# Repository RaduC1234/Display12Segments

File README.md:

# Display12Segments

Created in 2021. Uploaded here for arhive purposes.

The project includes an embedded device that i developed in 2021. Hardware created in Autodesk Eagle and software in MPLAB IDE and Visual Studio Code.

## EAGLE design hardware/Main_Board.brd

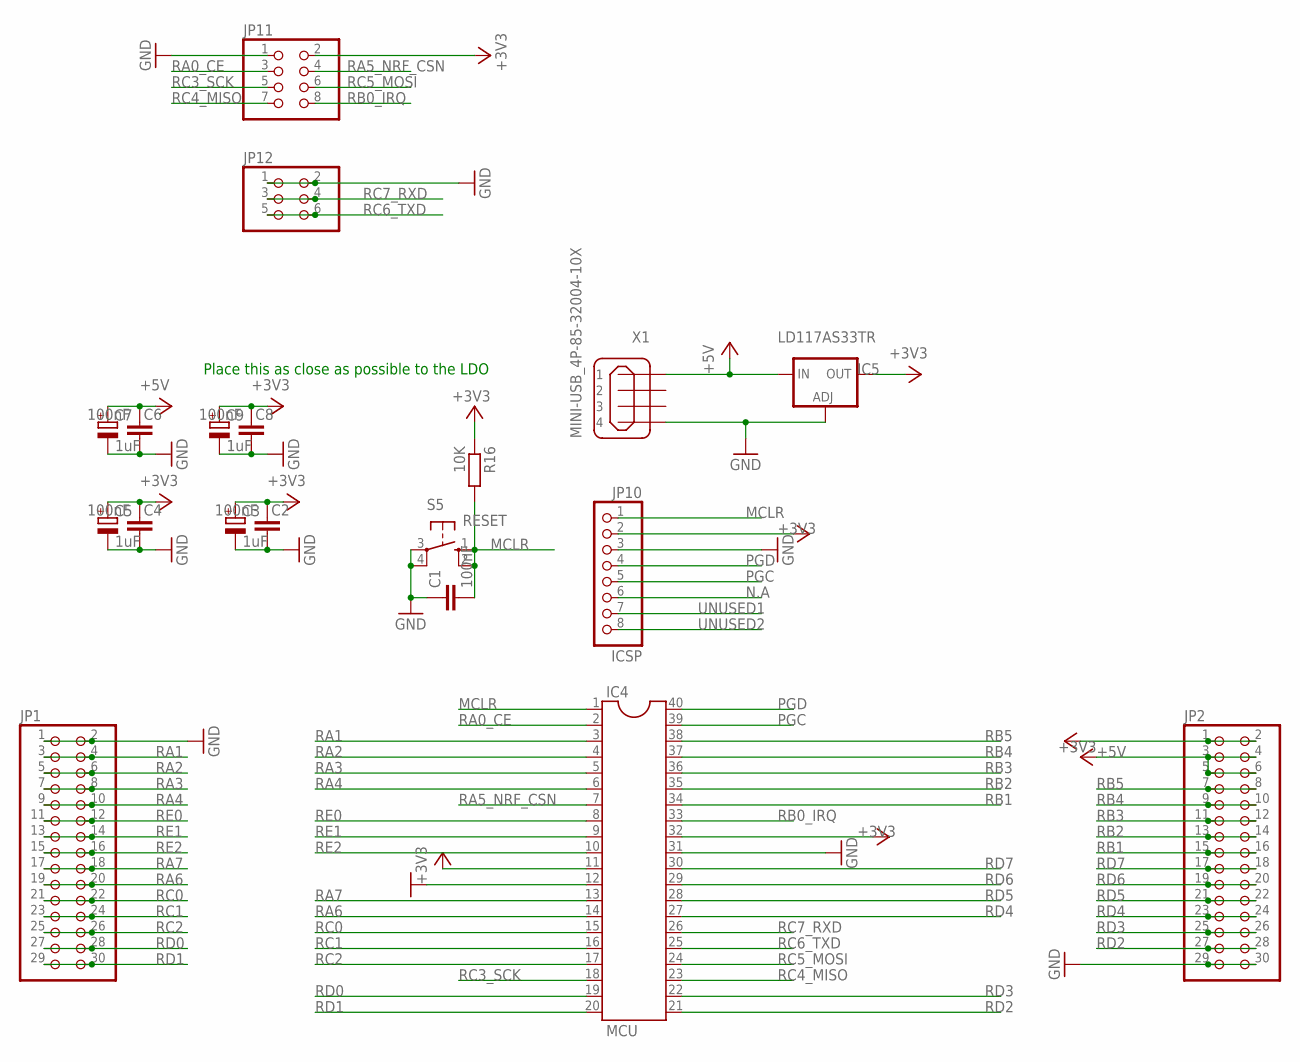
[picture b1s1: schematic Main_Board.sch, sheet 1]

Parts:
C1, C2, C4, C6, C8: 100nF; C025-025X050
C3, C5, C7, C9: 1uF; E1,8-4
IC4: MCU; DIL40
IC5: LD117AS33TR; SOT223
JP1, JP2: PINHD-2X15; 2X15
JP10: ICSP; 1X08
JP11: PINHD-2X4; 2X04
JP12: PINHD-2X3; 2X03
R16: 10K; 0207/10
S5: RESET; B3F-10XX
X1: MINI-USB_4P-85-32004-10X; 85-32004-10X

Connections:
+3V3: C2.2, C3.+, C4.2, C5.+, C8.2, C9.+, IC4.11, IC4.32, IC5.4 (OUT), JP2.1, JP2.2, JP10.2, JP11.2, R16.1; also elsewhere on the board
+5V: C6.2, C7.+, IC5.3 (IN), JP2.3, JP2.4, JP2.5, JP2.6, X1.1; also elsewhere on the board
GND: C1.1, C2.1, C3.-, C4.1, C5.-, C6.1, C7.-, C8.1, C9.-, IC4.12, IC4.31, IC5.1 (ADJ), JP1.1, JP1.2, JP2.29, JP2.30, JP10.3, JP11.1, JP12.1, JP12.2, S5.3, S5.4 (P1), X1.4; also elsewhere on the board
MCLR: C1.2, IC4.1, JP10.1, R16.2, S5.1 (S), S5.2 (S1)
N.A: JP10.6
PGC: IC4.39, JP10.5
PGD: IC4.40, JP10.4
RA0_CE: IC4.2, JP11.3
RA1: IC4.3, JP1.3, JP1.4
RA2: IC4.4, JP1.5, JP1.6
RA3: IC4.5, JP1.7, JP1.8
RA4: IC4.6, JP1.9, JP1.10
RA5_NRF_CSN: IC4.7, JP11.4
RA6: IC4.14, JP1.19, JP1.20
RA7: IC4.13, JP1.17, JP1.18
RB0_IRQ: IC4.33, JP11.8
RB1: IC4.34, JP2.15, JP2.16
RB2: IC4.35, JP2.13, JP2.14
RB3: IC4.36, JP2.11, JP2.12
RB4: IC4.37, JP2.9, JP2.10
RB5: IC4.38, JP2.7, JP2.8
RC0: IC4.15, JP1.21, JP1.22
RC1: IC4.16, JP1.23, JP1.24
RC2: IC4.17, JP1.25, JP1.26
RC3_SCK: IC4.18, JP11.5
RC4_MISO: IC4.23, JP11.7
RC5_MOSI: IC4.24, JP11.6
RC6_TXD: IC4.25, JP12.5, JP12.6
RC7_RXD: IC4.26, JP12.3, JP12.4
RD0: IC4.19, JP1.27, JP1.28
RD1: IC4.20, JP1.29, JP1.30
RD2: IC4.21, JP2.27, JP2.28
RD3: IC4.22, JP2.25, JP2.26
RD4: IC4.27, JP2.23, JP2.24
RD5: IC4.28, JP2.21, JP2.22
RD6: IC4.29, JP2.19, JP2.20
RD7: IC4.30, JP2.17, JP2.18
RE0: IC4.8, JP1.11, JP1.12
RE1: IC4.9, JP1.13, JP1.14
RE2: IC4.10, JP1.15, JP1.16
UNUSED1: JP10.7
UNUSED2: JP10.8

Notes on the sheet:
Place this as close as possible to the LDO

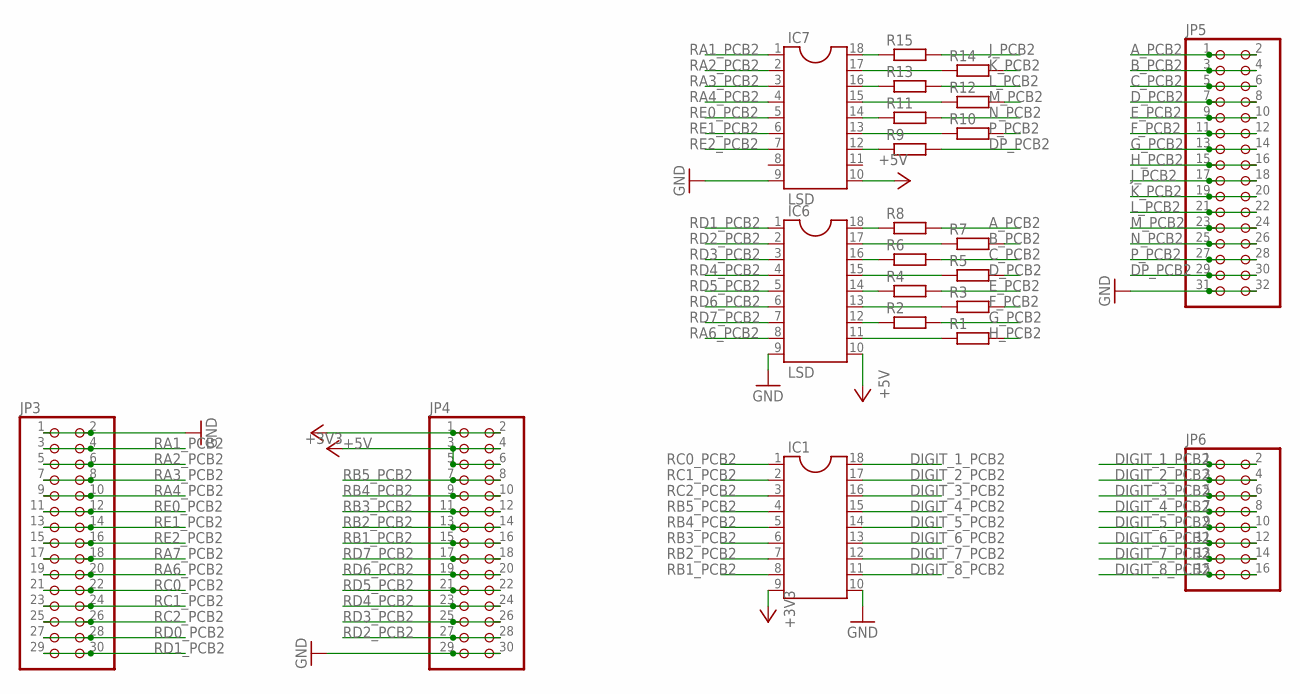
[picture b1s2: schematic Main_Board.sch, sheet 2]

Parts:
IC1: DIL18
IC6, IC7: LSD; DIL18
JP3, JP4: PINHD-2X15; 2X15
JP5: PINHD-2X16; 2X16
JP6: PINHD-2X8; 2X08
R1, R2, R3, R4, R5, R6, R7, R8, R9, R10, R11, R12, R13, R14, R15: R-EU_R0805; R0805

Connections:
+3V3: IC1.9, JP4.1, JP4.2; also elsewhere on the board
+5V: IC6.10, IC7.10, JP4.3, JP4.4, JP4.5, JP4.6; also elsewhere on the board
A_PCB2: JP5.1, JP5.2, R8.2
B_PCB2: JP5.3, JP5.4, R7.2
C_PCB2: JP5.5, JP5.6, R6.2
DIGIT_1_PCB2: IC1.18, JP6.1, JP6.2
DIGIT_2_PCB2: IC1.17, JP6.3, JP6.4
DIGIT_3_PCB2: IC1.16, JP6.5, JP6.6
DIGIT_4_PCB2: IC1.15, JP6.7, JP6.8
DIGIT_5_PCB2: IC1.14, JP6.9, JP6.10
DIGIT_6_PCB2: IC1.13, JP6.11, JP6.12
DIGIT_7_PCB2: IC1.12, JP6.13, JP6.14
DIGIT_8_PCB2: IC1.11, JP6.15, JP6.16
DP_PCB2: JP5.29, JP5.30, R9.2
D_PCB2: JP5.7, JP5.8, R5.2
E_PCB2: JP5.9, JP5.10, R4.2
F_PCB2: JP5.11, JP5.12, R3.2
GND: IC1.10, IC6.9, IC7.9, JP3.1, JP3.2, JP4.29, JP4.30, JP5.31, JP5.32; also elsewhere on the board
G_PCB2: JP5.13, JP5.14, R2.2
H_PCB2: JP5.15, JP5.16, R1.2
J_PCB2: JP5.17, JP5.18, R15.2
K_PCB2: JP5.19, JP5.20, R14.2
L_PCB2: JP5.21, JP5.22, R13.2
M_PCB2: JP5.23, JP5.24, R12.2
unnamed: IC6.18, R8.1
unnamed: IC6.17, R7.1
unnamed: IC6.16, R6.1
unnamed: IC6.15, R5.1
unnamed: IC6.14, R4.1
unnamed: IC6.13, R3.1
unnamed: IC6.12, R2.1
unnamed: IC6.11, R1.1
unnamed: IC7.18, R15.1
unnamed: IC7.17, R14.1
unnamed: IC7.16, R13.1
unnamed: IC7.15, R12.1
unnamed: IC7.14, R11.1
unnamed: IC7.13, R10.1
unnamed: IC7.12, R9.1
N_PCB2: JP5.25, JP5.26, R11.2
P_PCB2: JP5.27, JP5.28, R10.2
RA1_PCB2: IC7.1, JP3.3, JP3.4
RA2_PCB2: IC7.2, JP3.5, JP3.6
RA3_PCB2: IC7.3, JP3.7, JP3.8
RA4_PCB2: IC7.4, JP3.9, JP3.10
RA6_PCB2: IC6.8, JP3.19, JP3.20
RA7_PCB2: JP3.17, JP3.18
RB1_PCB2: IC1.8, JP4.15, JP4.16
RB2_PCB2: IC1.7, JP4.13, JP4.14
RB3_PCB2: IC1.6, JP4.11, JP4.12
RB4_PCB2: IC1.5, JP4.9, JP4.10
RB5_PCB2: IC1.4, JP4.7, JP4.8
RC0_PCB2: IC1.1, JP3.21, JP3.22
RC1_PCB2: IC1.2, JP3.23, JP3.24
RC2_PCB2: IC1.3, JP3.25, JP3.26
RD0_PCB2: JP3.27, JP3.28
RD1_PCB2: IC6.1, JP3.29, JP3.30
RD2_PCB2: IC6.2, JP4.27, JP4.28
RD3_PCB2: IC6.3, JP4.25, JP4.26
RD4_PCB2: IC6.4, JP4.23, JP4.24
RD5_PCB2: IC6.5, JP4.21, JP4.22
RD6_PCB2: IC6.6, JP4.19, JP4.20
RD7_PCB2: IC6.7, JP4.17, JP4.18
RE0_PCB2: IC7.5, JP3.11, JP3.12
RE1_PCB2: IC7.6, JP3.13, JP3.14
RE2_PCB2: IC7.7, JP3.15, JP3.16

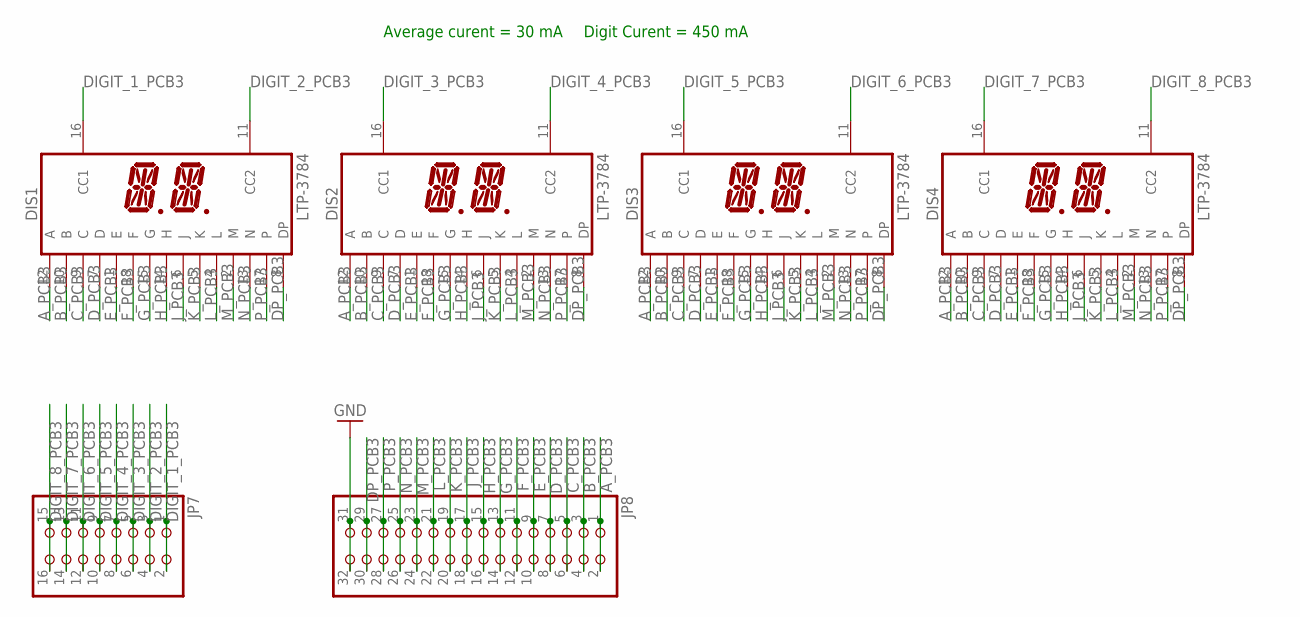
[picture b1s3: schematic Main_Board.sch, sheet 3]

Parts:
DIS1, DIS2, DIS3, DIS4: LTP-3784
JP7: PINHD-2X8; 2X08
JP8: PINHD-2X16; 2X16

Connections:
A_PCB3: DIS1.12 (A), DIS2.12 (A), DIS3.12 (A), DIS4.12 (A), JP8.1, JP8.2
B_PCB3: DIS1.10 (B), DIS2.10 (B), DIS3.10 (B), DIS4.10 (B), JP8.3, JP8.4
C_PCB3: DIS1.9 (C), DIS2.9 (C), DIS3.9 (C), DIS4.9 (C), JP8.5, JP8.6
DIGIT_1_PCB3: DIS1.16 (CC1), JP7.1, JP7.2
DIGIT_2_PCB3: DIS1.11 (CC2), JP7.3, JP7.4
DIGIT_3_PCB3: DIS2.16 (CC1), JP7.5, JP7.6
DIGIT_4_PCB3: DIS2.11 (CC2), JP7.7, JP7.8
DIGIT_5_PCB3: DIS3.16 (CC1), JP7.9, JP7.10
DIGIT_6_PCB3: DIS3.11 (CC2), JP7.11, JP7.12
DIGIT_7_PCB3: DIS4.16 (CC1), JP7.13, JP7.14
DIGIT_8_PCB3: DIS4.11 (CC2), JP7.15, JP7.16
DP_PCB3: DIS1.8 (DP), DIS2.8 (DP), DIS3.8 (DP), DIS4.8 (DP), JP8.29, JP8.30
D_PCB3: DIS1.7 (D), DIS2.7 (D), DIS3.7 (D), DIS4.7 (D), JP8.7, JP8.8
E_PCB3: DIS1.1 (E), DIS2.1 (E), DIS3.1 (E), DIS4.1 (E), JP8.9, JP8.10
F_PCB3: DIS1.18 (F), DIS2.18 (F), DIS3.18 (F), DIS4.18 (F), JP8.11, JP8.12
GND: JP8.31, JP8.32; also elsewhere on the board
G_PCB3: DIS1.15 (G), DIS2.15 (G), DIS3.15 (G), DIS4.15 (G), JP8.13, JP8.14
H_PCB3: DIS1.14 (H), DIS2.14 (H), DIS3.14 (H), DIS4.14 (H), JP8.15, JP8.16
J_PCB3: DIS1.6 (J), DIS2.6 (J), DIS3.6 (J), DIS4.6 (J), JP8.17, JP8.18
K_PCB3: DIS1.5 (K), DIS2.5 (K), DIS3.5 (K), DIS4.5 (K), JP8.19, JP8.20
L_PCB3: DIS1.4 (L), DIS2.4 (L), DIS3.4 (L), DIS4.4 (L), JP8.21, JP8.22
M_PCB3: DIS1.2 (M), DIS2.2 (M), DIS3.2 (M), DIS4.2 (M), JP8.23, JP8.24
N_PCB3: DIS1.13 (N), DIS2.13 (N), DIS3.13 (N), DIS4.13 (N), JP8.25, JP8.26
P_PCB3: DIS1.17, DIS2.17, DIS3.17, DIS4.17, JP8.27, JP8.28

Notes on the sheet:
Average curent = 30 mA
Digit Curent = 450 mA

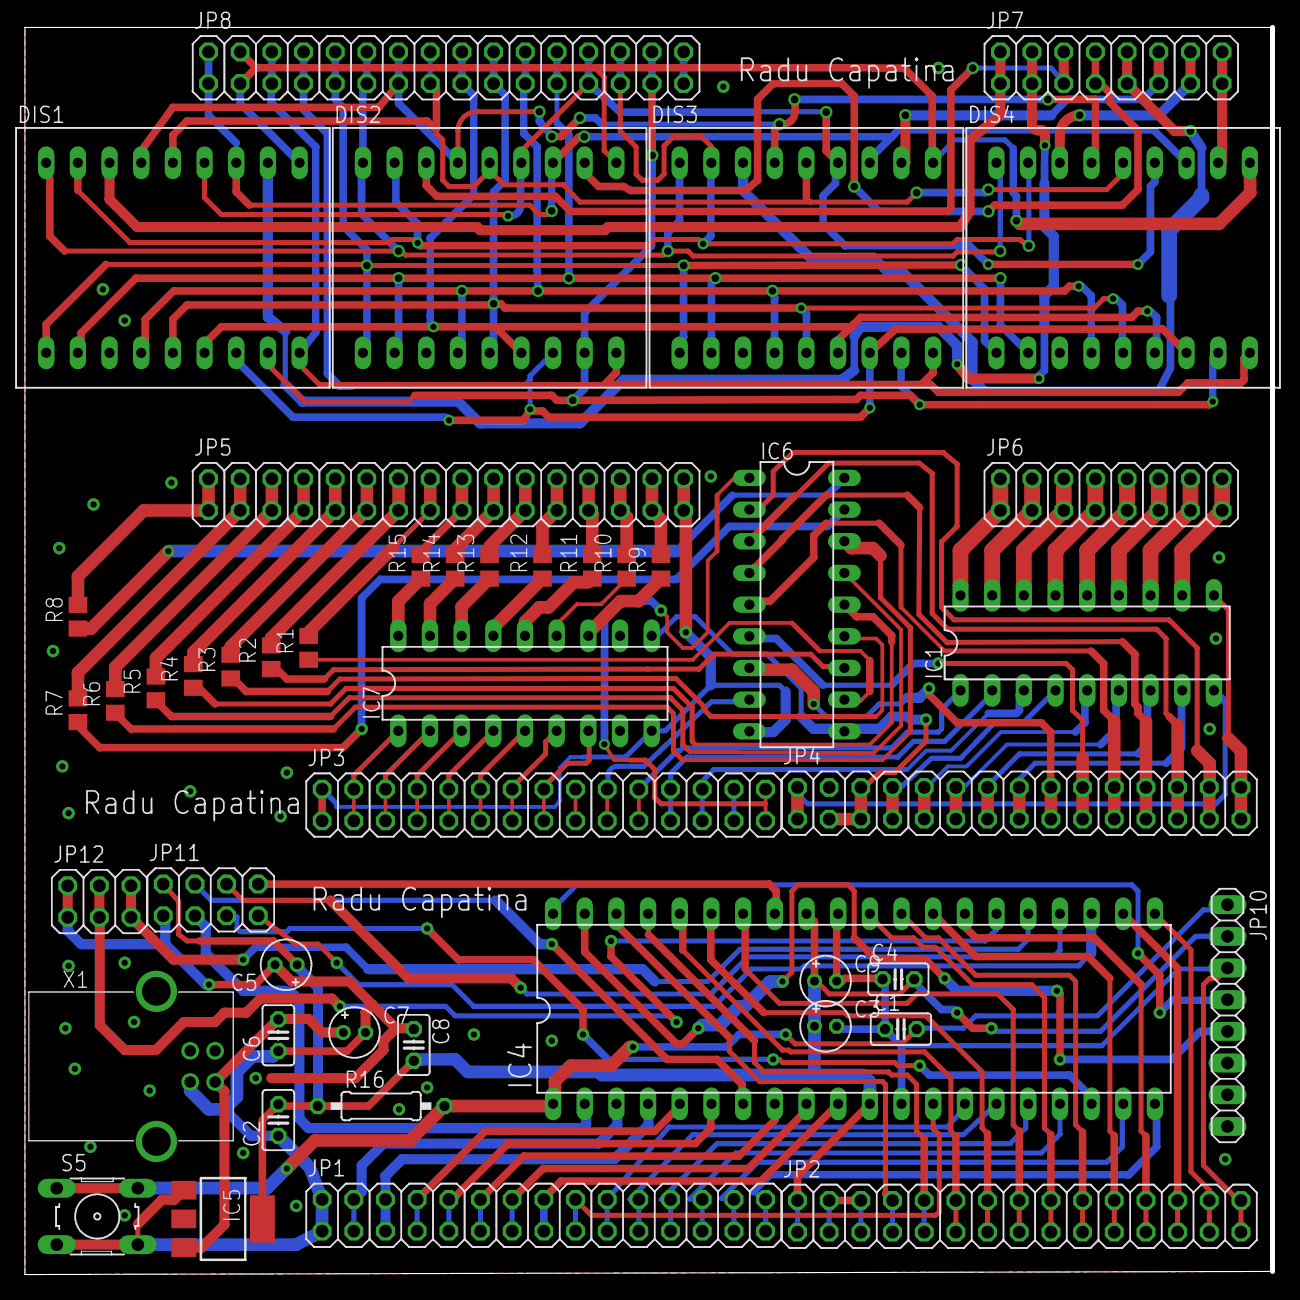
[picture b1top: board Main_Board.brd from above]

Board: 2 copper layers, 99.8 x 99.8 mm, 47 parts (0 on the bottom side), 125 nets.

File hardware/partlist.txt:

Partlist

Exported from Main_Board.sch at 6/27/2021 6:11:27 AM

EAGLE Version 6.3.0 Copyright (c) 1988-2012 CadSoft

Assembly variant: 

Part     Value                    Device                   Package      Library               Sheet

*C1       100nF                    C-EU025-025X050          C025-025X050 rcl                   1
*C2       100nF                    C-EU025-025X050          C025-025X050 rcl                   1
*C6       100nF                    C-EU025-025X050          C025-025X050 rcl                   1
*C4       100nF                    C-EU025-025X050          C025-025X050 rcl                   1
*C8       100nF                    C-EU025-025X050          C025-025X050 rcl                   1
*C5       1uF                      CPOL-EUE1.8-4            E1,8-4       rcl                   1
*C7       1uF                      CPOL-EUE1.8-4            E1,8-4       rcl                   1
*C3       1uF                      CPOL-EUE1.8-4            E1,8-4       rcl                   1
*C9       1uF                      CPOL-EUE1.8-4            E1,8-4       rcl                   1
//DIS1     LTP-3784                 LTP-3784                 LTP-3784     liteon               3
//DIS2     LTP-3784                 LTP-3784                 LTP-3784     liteon               3
//DIS3     LTP-3784                 LTP-3784                 LTP-3784     liteon               3
//DIS4     LTP-3784                 LTP-3784                 LTP-3784     liteon               3
*IC1                               DIL18                    DIL18        ic-package            2
cuplet de 8 canale darlington cu capabilitate de sourceing
https://ro.farnell.com/micrel-semiconductor/mic2981-82yn/sou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
BB**IC4      MCU                      DIL40                    DIL40        ic-package         1
//IC5      LD117AS33TR              LD117AS33TR              SOT223       v-reg                1
//IC6      LSD                      DIL18                    DIL18        ic-package           2
//IC7      LSD                      DIL18                    DIL18        ic-package           2
*JP1                               PINHD-2X15               2X15         pinhead               1
*JP2                               PINHD-2X15               2X15         pinhead               1
*JP3                               PINHD-2X15               2X15         pinhead               2
*JP4                               PINHD-2X15               2X15         pinhead               2
*JP5                               PINHD-2X16               2X16         pinhead               2
*JP6                               PINHD-2X8                2X08         pinhead               2
*JP7                               PINHD-2X8                2X08         pinhead               3
*JP8                               PINHD-2X16               2X16         pinhead               3
*JP10     ICSP                     PINHD-1X8                1X08         pinhead               1
*JP11                              PINHD-2X4                2X04         pinhead               1
*JP12                              PINHD-2X3                2X03         pinhead               1
//R1                                R-EU_R0805               R0805        rcl                  2
//R2                                R-EU_R0805               R0805        rcl                  2
//R3                                R-EU_R0805               R0805        rcl                  2
//R4                                R-EU_R0805               R0805        rcl                  2
//R5                                R-EU_R0805               R0805        rcl                  2
//R6                                R-EU_R0805               R0805        rcl                  2
//R7                                R-EU_R0805               R0805        rcl                  2
//R8                                R-EU_R0805               R0805        rcl                  2
//R9                                R-EU_R0805               R0805        rcl                  2
//R10                               R-EU_R0805               R0805        rcl                  2
//R11                               R-EU_R0805               R0805        rcl                  2
//R12                               R-EU_R0805               R0805        rcl                  2
//R13                               R-EU_R0805               R0805        rcl                  2
//R14                               R-EU_R0805               R0805        rcl                  2
//R15                               R-EU_R0805               R0805        rcl                  2
*R16      10K                      R-EU_0207/10             0207/10      rcl                   1
*S5       RESET                    10-XX                    B3F-10XX     switch-omron          1
//X1       MINI-USB_4P-85-32004-10X MINI-USB_4P-85-32004-10X 85-32004-10X con-cypressindustries 1
